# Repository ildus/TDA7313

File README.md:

# TDA7313 library for Arduino

## About

TDA7313 is digital controlled stereo audio processor. Features:

* 3 stereo inputs
* 4 speaker attenuators
* Treble and bass control
* Loudness function
* Other features

This library implements all features of TDA7313 by I2C protocol.

## Tests

	mkdir build && cd build
	cmake ../
	make && ./test

## Dependencies

* cmake for testing

* https://github.com/rpavlik/StandardCplusplus

## PCB

I've also included PCB footprints in Eagle format (https://cadsoft.io). It includes all elements from datasheet and voltage regulator to 9V.

![PCB]
(https://habrastorage.org/files/fc1/a0f/32b/fc1a0f32b7794bdb8be0d9e7b7a40666.png)

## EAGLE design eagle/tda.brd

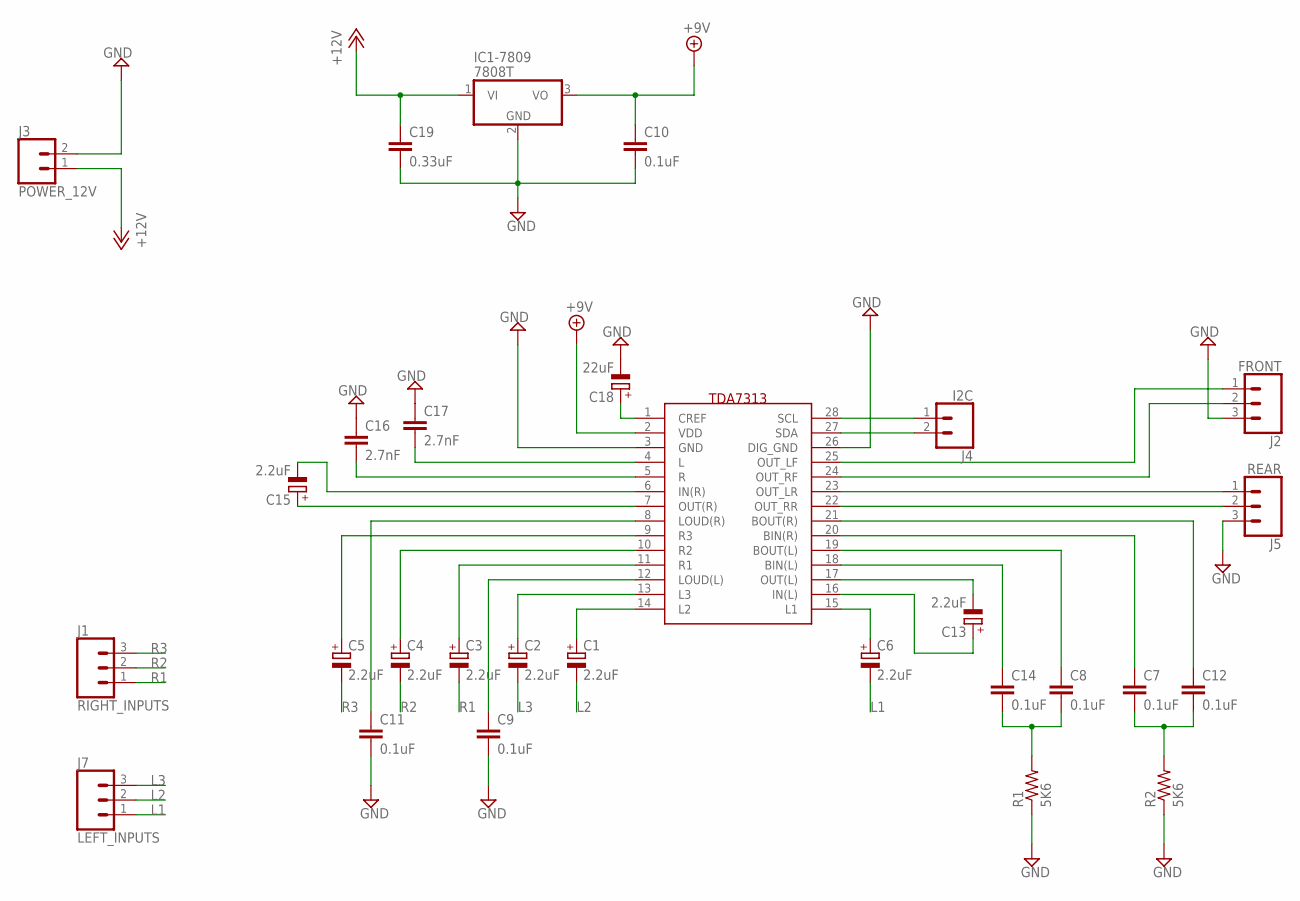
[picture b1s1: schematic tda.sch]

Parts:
C1, C2, C3, C4, C5, C6, C13, C15: 2.2uF; E2-4
C7, C8, C9, C10, C11, C12, C14: 0.1uF; C0805
C16, C17: 2.7nF; C0805
C18: 22uF; E2-4
C19: 0.33uF; C0805
IC1-7809: 7808T; TO220H
J1: RIGHT_INPUTS; 1X03_LONGPADS
J2: FRONT; 1X03_LONGPADS
J3: POWER_12V; 1X02_LOCK_LONGPADS
J4: I2C; 1X02_LOCK_LONGPADS
J5: REAR; 1X03_LONGPADS
J7: LEFT_INPUTS; 1X03_LONGPADS
R1, R2: 5K6; 0207/10
U$1: TDA7313_SO28; SO28

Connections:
+9V: C10.1, IC1-7809.3 (VO), U$1.2 (VDD)
+12V: C19.1, IC1-7809.1 (VI), J3.1
GND: C9.2, C10.2, C11.2, C16.1, C17.1, C18.-, C19.2, IC1-7809.2 (GND), J2.3, J3.2, J5.3, R1.1, R2.1, U$1.3 (GND), U$1.26 (DIG_GND)
L1: C6.-, J7.1
L2: C1.-, J7.2
L3: C2.-, J7.3
unnamed: C1.+, U$1.14 (L2)
unnamed: C2.+, U$1.13 (L3)
unnamed: C3.+, U$1.11 (R1)
unnamed: C4.+, U$1.10 (R2)
unnamed: C5.+, U$1.9 (R3)
unnamed: C6.+, U$1.15 (L1)
unnamed: C9.1, U$1.12 (LOUD(L))
unnamed: C11.1, U$1.8 (LOUD(R))
unnamed: C13.-, U$1.17 (OUT(L))
unnamed: C13.+, U$1.16 (IN(L))
unnamed: C8.2, C14.2, R1.2
unnamed: C14.1, U$1.18 (BIN(L))
unnamed: C8.1, U$1.19 (BOUT(L))
unnamed: C7.2, C12.2, R2.2
unnamed: C7.1, U$1.20 (BIN(R))
unnamed: C12.1, U$1.21 (BOUT(R))
unnamed: C15.+, U$1.7 (OUT(R))
unnamed: C15.-, U$1.6 (IN(R))
unnamed: C16.2, U$1.5 (R)
unnamed: C17.2, U$1.4 (L)
unnamed: C18.+, U$1.1 (CREF)
OUT_LF: J2.1, U$1.25 (OUT_LF)
OUT_LR: J5.1, U$1.23 (OUT_LR)
OUT_RF: J2.2, U$1.24 (OUT_RF)
OUT_RR: J5.2, U$1.22 (OUT_RR)
R1: C3.-, J1.1
R2: C4.-, J1.2
R3: C5.-, J1.3
SCL: J4.1, U$1.28 (SCL)
SDA: J4.2, U$1.27 (SDA)

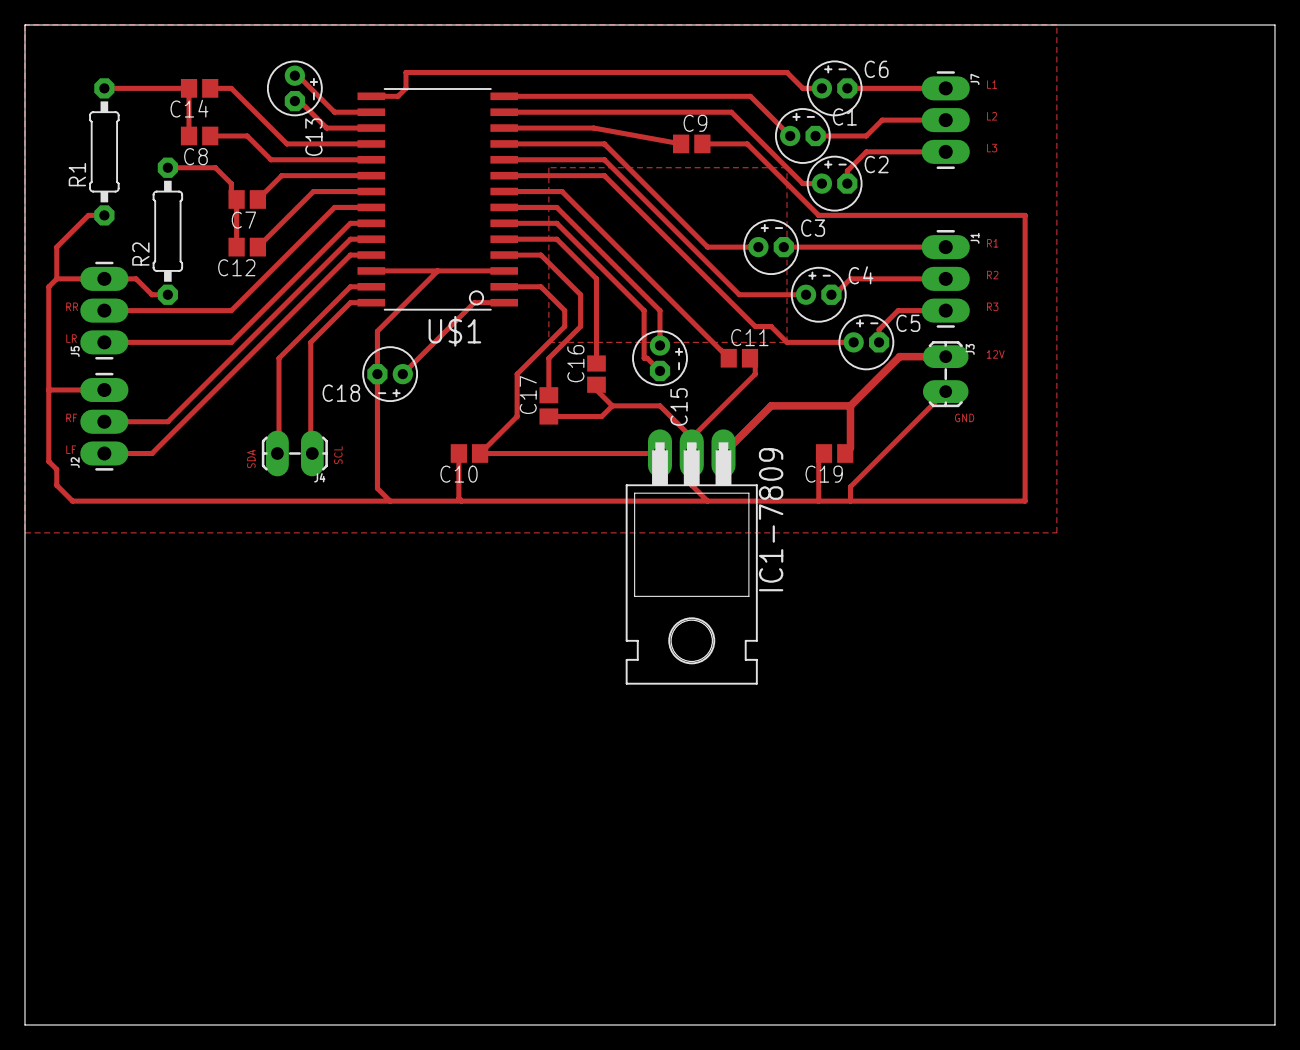
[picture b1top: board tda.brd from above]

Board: 2 copper layers, 100.0 x 80.0 mm, 29 parts (0 on the bottom side), 36 nets.

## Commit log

2017-01-15 Add base functions
2017-01-17 Add tests
2017-01-17 Fix compilation as arduino library
2017-01-17 Add few volume functions
2017-01-17 Add eagle files, fix arduino checking
2017-01-17 Add bass and treble functions
2017-01-17 Add README
2017-01-17 Add git attributes file
2017-04-24 Add travis configuration
2017-04-24 Add compilers to travis configuration
2017-04-24 Add build status to README
2017-04-24 Make changes for travis
2017-04-24 Leave only gcc in testing

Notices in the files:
parts and their libraries:
SparkFun-Connectors: Licensing: Creative Commons ShareAlike 4.0 International - https://creativecommons.org/licenses/by-sa/4.0
